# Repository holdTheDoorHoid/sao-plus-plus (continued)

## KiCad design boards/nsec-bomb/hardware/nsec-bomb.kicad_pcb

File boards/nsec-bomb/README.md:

# NorthSec Bomb — SAO++ edition

The circuit is **Sao_Bomb**, one of the add-ons made for the **NorthSec 2025** badge by the **NorthSec badge team**: https://github.com/nsec/nsec-badge/tree/nsec25/hw/2025/sao/Sao_Bomb (commit 0ea779f, 2025-07-14). Licence: **MIT** (their `LICENSE` is kept in [original/LICENSE](original/LICENSE); no file of this board states an exception).

**The outline and the front art are SAO++'s own drawing** (CC-BY-SA-4.0, [art/nsec-bomb-front.svg](art/nsec-bomb-front.svg)), not NorthSec's. NorthSec drew their board over a picture of a cartoon time bomb whose owner nobody here can identify, so their outline and art are not used and not kept in this repository ([original/README.md](original/README.md) lists exactly what was cut).

> **One art question is still open, and it is the owner's call before anything is sold:** the "nsec 2025" logo on the back is NorthSec's event branding. The MIT licence covers the file, not the use of their name and mark on boards someone else sells. Ask NorthSec, or take the logo off.

## What NorthSec's original is

Their repository does not describe it, so this is read from the files:

- A 53 × 38 mm add-on shaped like a bundle of dynamite with a clock, badge power only: a 2×3 SMD header, four LEDs soldered on the front by hand, each with a 330 Ω resistor.
- **Eight small plated holes, not nine and not sockets.** The survey read them as "pin sockets" because the maker used a socket footprint, but their parts list gives them a quantity of 0: nothing was fitted. Four holes are on the 3.3 V supply ("3v3") and four each lead to one LED ("Conn1" … "Conn4").
- **No LED is connected to anything until you add a wire.** A wire from a 3v3 hole to a Conn hole lights that LED. Those are the bomb's wires; cut one and its light goes out. There is no chip and no game logic: whatever game was played with it at the event was played by people.
- On the back, the "nsec 2025" logo and a 5 × 5 mm white square (purpose not recorded).

## What SAO++ makes of it

The same circuit and the same wire trick on a newly drawn board, working from **either** the badge **or** its own coin cell.

**The drawing (front):** three sticks of dynamite stacked flat, 54 × 38 mm, the middle one 3.5 mm shorter at each end. Two white bands of tape hold them together. "TNT" on the top stick, "DANGER" on the bottom one. Strapped across the middle is a timer box: a white frame with four screws and a display reading **00:07** in bare (gold-plated) copper. Each end of the top and bottom sticks is a detonator: a small bare window with a red LED glowing behind it and, beside it, a numbered wire terminal (1–4). The timer carries four "+" terminals. The builder's own wires, from timer to detonators, finish the picture.

| | NorthSec original (2025) | SAO++ rev A |
|---|---|---|
| Outline and art | Traced by the maker from a third-party picture | Drawn from scratch by `hardware/build_board.py` |
| Connector | 2×3 SMD header, centre of the back | 6-pin SAO v1.69bis shrouded, keyed SMD connector, key slot up, mid-height, 10.5 mm right of centre (front view) |
| Power | Badge only | Slide switch in the middle of the bottom edge: **SAO / OFF / BAT**. CR2032 clip on the back; the cell slides in from the top edge |
| Lights | Four hand-soldered 1206 LEDs on the front | Four **red** LEDs on the back, shining through the board at the four detonators |
| Resistors | 330 Ω (about 4 mA per LED) | 1.3 kΩ (about 1 mA per LED, so a cell lasts) |
| Wire points | Eight 0.7 mm plated holes | Eight **1.6 mm square solder pads, no hole** |
| Back | Logo, white square | Same logo and square, same size. Labels: SAO / OFF / BAT, "CR2032 + UP", pin 1, "BOMB SAO++ rA", "circuit: NorthSec 2025 (MIT)" |

**How to arm it:** solder a short piece of wire on the front from any **+** pad on the timer to a numbered pad. Wire 1 lights the upper-left detonator, 2 upper right, 3 lower left, 4 lower right. Leave the wires looped up off the board so they can be cut. A wire can only ever join the supply to a resistor, so no wiring mistake between these pads can short anything or reach the coin cell.

**Why pads instead of holes:** a wire soldered through a hole leaves a stub on the back, where the coin cell has to slide along the board and rest. Pads keep the back flat. Wires soldered on a pad are easier to fit but may be weaker when tugged; that is untested.

**Parts shared with the rest of SAO++:** connector, switch, cell clip, red through-board LED and 1.3 kΩ resistor: all reels other boards already use. **No new part.** The wire pads are bare copper.

**Battery life (calculated, not measured):** four red LEDs at about 1 mA each is about 4 mA, so a CR2032 should last roughly 35–50 hours with all four wires in place.

## How it fits

Drawing the outline ourselves removed the squeeze the traced outline had:

- **Switch:** the bottom edge is straight for 49 mm, so the switch sits in the middle of it with its knob 1.05 mm past the edge.
- **Cell:** the top edge is straight too. The cell slides in 5 mm from it, between the upper-left LED (0.9 mm clear of the cell's path) and the logo.
- **Clip and connector** sit side by side with 1.8 mm between the clip and the connector's shroud; no keep-out boxes overlap, so the board needs no rule exceptions.
- **LEDs** lie along their sticks, 3.6 mm in from each end, each with its resistor 3.1 mm toward the middle of the board.
- **Front copper:** the supply reaches the four + pads by a thin track that runs under the bottom line of the timer's frame and up each side of the display between the pads; each numbered pad has a 3 mm track to a tiny covered via. Under solder mask these show only faintly.

## Things to check on the first prototype

1. **Wire pads.** Solder four wires, tug them, cut them. If pads lift, make the pads larger or go back to plated holes with badge power only.
2. **Light through the board.** Each LED shines through 1.6 mm of board into a 3.2 × 1.6 mm bare window. `SAOPP-LED-10` is still marked "verify: brightness through 1.6 mm board at 1 mA" in the parts list; this board does not settle that until one is built. If dim, R1–R4 can become 330 Ω (SAOPP-R-02, already approved): about 4 mA each, NorthSec's own value, and well under a day per cell.
3. **Display digits.** The 00:07 is bare copper with strokes 0.6 mm wide, each in its own opening in the solder mask. Check they come out crisp, and that the fab does not object to copper that is connected to nothing.
4. **Switch.** Which way the knob sits for position 1 (the labels assume "knob toward SAO = badge power"; if not, swap the SAO and BAT labels).
5. **Cell clip direction.** The clip fits its pads both ways round; its open side must face the **top** edge. Tell the assembler.
6. **Pin 1 position** against a real v1.69bis badge (same corner as every other SAO++ board).
7. **Hanging.** The connector is 10.5 mm right of centre (front view) with the cell on the other side; check how the board hangs and that it does not strain the badge socket.
8. **Mask colour.** Red is the obvious choice (the SVG in `art/` shows it); the renders above use KiCad's default green.

## Files

- `hardware/nsec-bomb.kicad_pro` — KiCad 10 project. ERC: 0 issues. DRC: 0 errors, 0 warnings, 0 unconnected, schematic matches board.
- `hardware/build_board.py` — draws the whole board: the ART section holds every number of the outline and front art, the PLACEMENT section every part position. It reads only `circuit.json` and the footprint libraries, nothing from `original/`. It also writes `art/nsec-bomb-front.svg` and `hardware/outline.json`.
- `art/nsec-bomb-front.svg` — the front as a picture (red mask, white silkscreen, gold copper), written by the build script.
- `hardware/circuit.json` — the circuit as data; `tools/gen_schematic.py nsec-bomb` then `hardware/fix_schematic.py` (marks the eight bare pads "not in BOM") make the schematic.
- `hardware/nsec-bomb.kicad_dru` — one rule, so the copper display digits are not flagged for being art.
- `hardware/parts_local.py`, `hardware/nsec-bomb-local.pretty/` — the wire pad (bare copper, nothing to buy) and an unchanged copy of NorthSec's logo footprint.
- `production/` — everything a board house needs, for one board (`single/`) and a 2×2 panel (`panel/`). Start with [production/README.md](production/README.md).
- `original/` — NorthSec's circuit files (schematic, footprints, parts list, and the board file with the traced outline and art cut out). See [original/README.md](original/README.md).

## Parts cost (parts only; list prices as dated in docs/parts.md, not re-checked for this board)

| Part | Qty | Each @ ~100 boards |
|---|---|---|
| Connector XFCN BH254VS-6P (LCSC C492445) | 1 | $0.10 |
| Switch C&K PCM13SMTR (Digikey) | 1 | ~$0.90 |
| CR2032 clip TE BAT-HLD-001 (LCSC C7501066) | 1 | $0.61 |
| Red through-board LED LTST-C230KRKT (LCSC C125107) | 4 | $0.037 |
| Resistor 0603 1.3 kΩ (LCSC C22767) | 4 | <$0.01 |
| **Total** | | **about $1.80** |

Not included: the CR2032 cell, the bare board (54 × 38 mm) and the jumper wire.

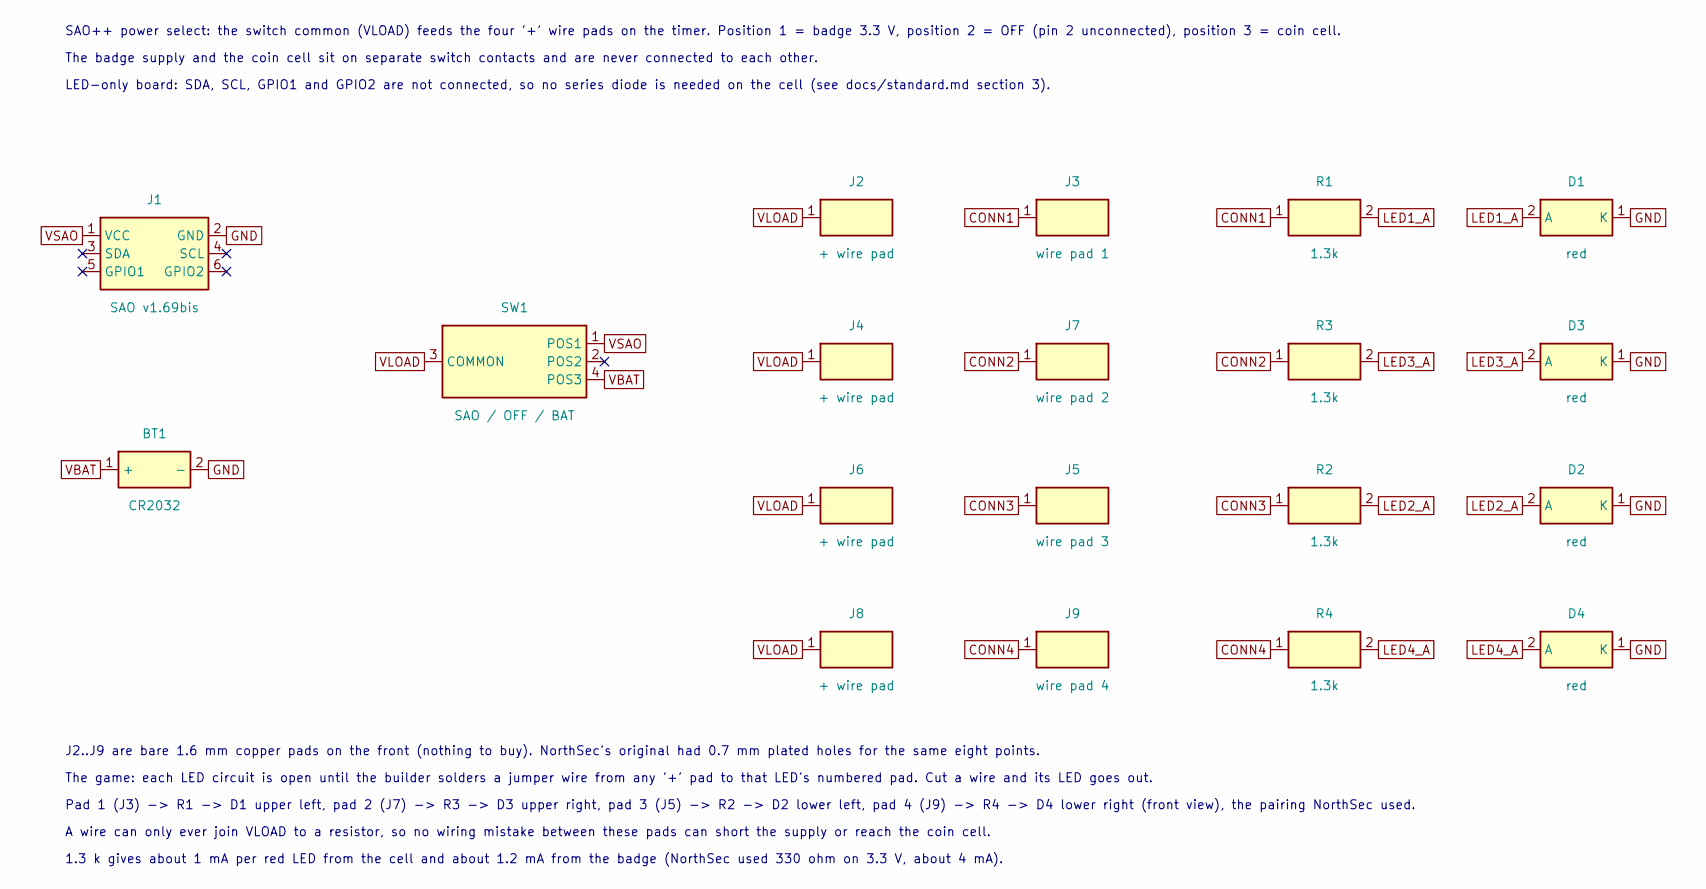
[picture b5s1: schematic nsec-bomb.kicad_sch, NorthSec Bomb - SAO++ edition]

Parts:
BT1: CR2032; SAOPP_BAT-01_CR2032_SMD_TE_BAT-HLD-001; MPN BAT-HLD-001; LCSC C7501066
D1, D2, D3, D4: red; SAOPP_LED-10_1206_ReverseMount_ThroughBoard; MPN LTST-C230KRKT; LCSC C125107
J1: SAO v1.69bis; SAOPP_CONN-01_BoxHeader_2x03_P2.54mm_SMD_XFCN_BH254VS-6P; MPN BH254VS-6P; LCSC C492445
J2, J4, J6, J8: + wire pad; WirePad_1.6x1.6mm; MPN none: bare pad, nothing fitted
J3: wire pad 1; WirePad_1.6x1.6mm; MPN none: bare pad, nothing fitted
J5: wire pad 3; WirePad_1.6x1.6mm; MPN none: bare pad, nothing fitted
J7: wire pad 2; WirePad_1.6x1.6mm; MPN none: bare pad, nothing fitted
J9: wire pad 4; WirePad_1.6x1.6mm; MPN none: bare pad, nothing fitted
R1, R2, R3, R4: 1.3k; SAOPP_R_0603_1608Metric; MPN 0603WAF1301T5E; LCSC C22767
SW1: SAO / OFF / BAT; SAOPP_SW-01_Slide_SP3T_CK_PCM13SMTR; MPN PCM13SMTR; LCSC C221842

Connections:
CONN1: J3.1, R1.1
CONN2: J7.1, R3.1
CONN3: J5.1, R2.1
CONN4: J9.1, R4.1
GND: BT1.2 (-), D1.1 (K), D2.1 (K), D3.1 (K), D4.1 (K), J1.2 (GND)
LED1_A: D1.2 (A), R1.2
LED2_A: D2.2 (A), R2.2
LED3_A: D3.2 (A), R3.2
LED4_A: D4.2 (A), R4.2
VBAT: BT1.1 (+), SW1.4 (POS3)
VLOAD: J2.1, J4.1, J6.1, J8.1, SW1.3 (COMMON)
VSAO: J1.1 (VCC), SW1.1 (POS1)

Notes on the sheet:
SAO++ power select: the switch common (VLOAD) feeds the four '+' wire pads on the timer. Position 1 = badge 3.3 V, position 2 = OFF (pin 2 unconnected), position 3 = coin cell.
The badge supply and the coin cell sit on separate switch contacts and are never connected to each other.
LED-only board: SDA, SCL, GPIO1 and GPIO2 are not connected, so no series diode is needed on the cell (see docs/standard.md section 3).
J2..J9 are bare 1.6 mm copper pads on the front (nothing to buy). NorthSec's original had 0.7 mm plated holes for the same eight points.
The game: each LED circuit is open until the builder solders a jumper wire from any '+' pad to that LED's numbered pad. Cut a wire and its LED goes out.
Pad 1 (J3) -> R1 -> D1 upper left, pad 2 (J7) -> R3 -> D3 upper right, pad 3 (J5) -> R2 -> D2 lower left, pad 4 (J9) -> R4 -> D4 lower right (front view), the pairing NorthSec used.
A wire can only ever join VLOAD to a resistor, so no wiring mistake between these pads can short the supply or reach the coin cell.
1.3 k gives about 1 mA per red LED from the cell and about 1.2 mA from the badge (NorthSec used 330 ohm on 3.3 V, about 4 mA).

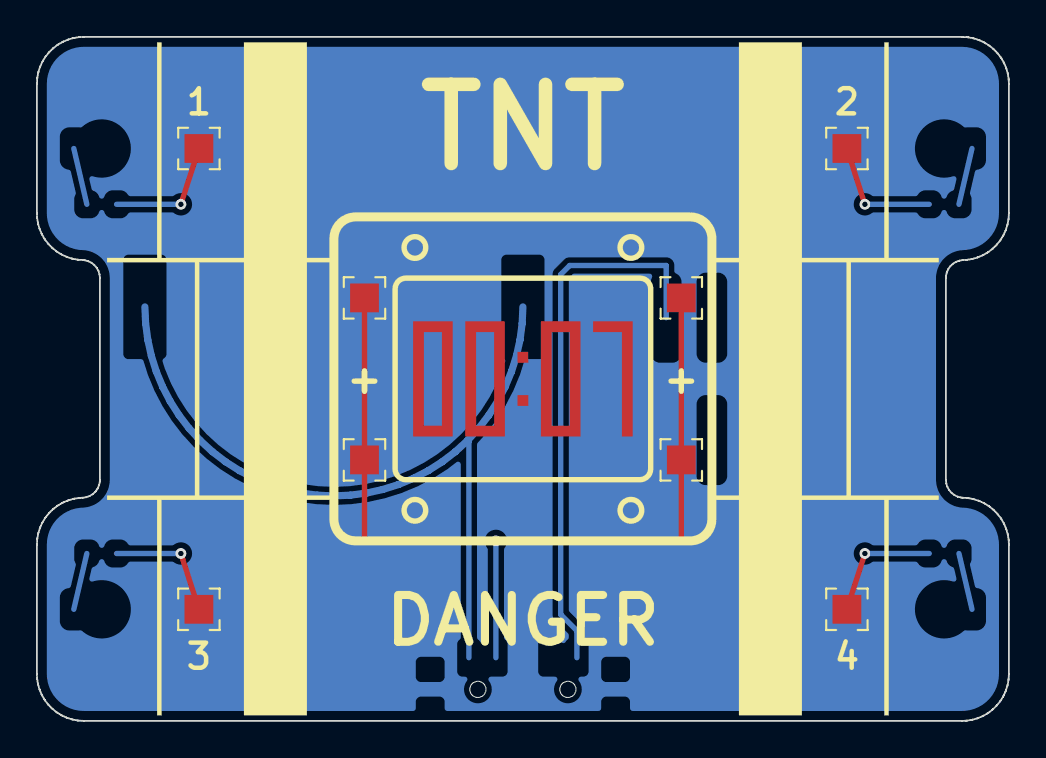
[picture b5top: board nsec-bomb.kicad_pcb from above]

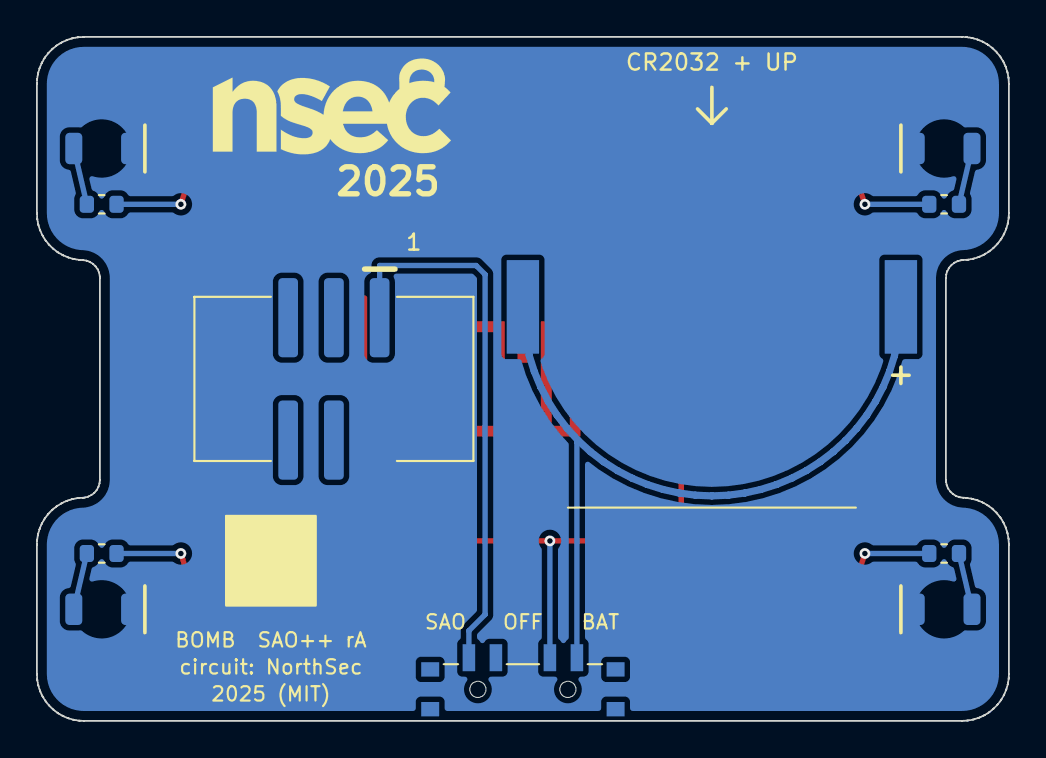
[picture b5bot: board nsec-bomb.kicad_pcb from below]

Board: 2 copper layers, 54.0 x 38.0 mm, 19 parts (11 on the bottom side), 12 nets.

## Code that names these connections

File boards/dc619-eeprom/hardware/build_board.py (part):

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  - J1, the 6-pin SAO v1.69bis header
  - U1, an AT24C02N I2C EEPROM (SOIC-8): A0 A1 A2 to GND (address 0x50), WP to GND (writable), VCC to SAO pin 1,
    SDA / SCL straight to SAO pins 3 / 4. No pull-ups, no supply capacitor
  - R1 4.7k from SAO pin 5 (GPIO1) to LED D2 to GND, and R2 4.7k from SAO pin 6 (GPIO2) to LED D1 to GND: two lights
    the BADGE switches on by driving its GPIO lines high
There is no battery and no switch on it. So everything drawn here (outline, placement, routing, front artwork) is
SAO++'s own; only the circuit is the maker's.
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CONN = (12.0, 9.2)          # centred left-right; pads start 3.6 mm from the top edge, body 4.36 mm from the sides
U1_AT = (11.2, 17.6)        # EEPROM, just below the connector
C1_AT = (7.6, 17.775)       # its supply capacitor, beside it
R1_AT = (2.3, 13.6)         # GPIO1 resistor, in the left margin beside the connector
R2_AT = (17.2, 16.2)        # GPIO2 resistor, below the connector
D2_AT = (4.4, 19.0)         # GPIO1 light, lower left (front view)
D1_AT = (19.6, 19.0)        # GPIO2 light, lower right
VIA_U1 = (11.2, 20.2)       # ground via below the EEPROM
VIA_J1 = (5.6, 9.25)        # ground via under the connector body

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_NS = uuid.UUID("5a0b1b15-0000-4000-8000-00000000a011")          # same namespace as tools/gen_schematic.py

# the maker's circuit, checked against the schematic picture every build
assert PADNETS["J1"] == {"1": "VSAO", "2": "GND", "3": "SDA", "4": "SCL", "5": "SAO_GPIO1", "6": "SAO_GPIO2"}
assert PADNETS["U1"] == {"1": "SCL", "2": "GND", "3": "SDA", "4": "VSAO", "5": "GND"}     # SOT-23-5: 5 = WP, tied low
assert all(len(d) == len(PINNAMES[r]) for r, d in PADNETS.items()), "every pin is wired on this board"

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conn = place("J1", CONN, ("1", (CONN[0] - 2.54, CONN[1] - 3.4)))          # VCC top-left in front view = key slot up
u1 = place("U1", U1_AT, ("1", (U1_AT[0] + 1.1375, U1_AT[1] - 0.95)))       # SCL / GND / SDA column on the right
c1 = place("C1", C1_AT, ("1", (C1_AT[0], C1_AT[1] + 0.775)))               # supply pad at the bottom, level with U1 pin 4
r1 = place("R1", R1_AT, ("1", (R1_AT[0], R1_AT[1] - 0.825)))               # GPIO1 enters at the top
r2 = place("R2", R2_AT, ("1", (R2_AT[0] - 0.825, R2_AT[1])))               # GPIO2 enters on the left
d2 = place("D2", D2_AT, ("2", (D2_AT[0] - 1.55, D2_AT[1])))                # anode toward the left edge
d1 = place("D1", D1_AT, ("2", (D1_AT[0] - 1.55, D1_AT[1])))                # anode toward the middle
LEDS = {"D1": D1_AT, "D2": D2_AT}

# connector pin order, as docs/standard.md section 1 draws it (seen from the front it is mirrored: VCC SDA GPIO1 / GND SCL GPIO2)
def near(a, b, tol=0.002):
    return abs(a[0] - b[0]) < tol and abs(a[1] - b[1]) < tol

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u3 = pp(u1, "3")
SX = ux + 2.7
route("SDA", [pp(conn, "3"), (cx, MID), (LANE_R, MID + 1.27), (LANE_R, BELOW + 0.2), (SX, BELOW + 0.2 + (SX - LANE_R)), (SX, u3[1]), u3])
# GPIO2: pin 6 (bottom right) -> R2 -> the right-hand light
r2a, r2b = pp(r2, "1"), pp(r2, "2")
route("SAO_GPIO2", [pp(conn, "6"), (cx + 2.54, r2a[1] - 0.8), (cx + 2.54 + 0.8, r2a[1]), r2a])
d1a = pp(d1, "2")
route("LED1_A", [r2b, (d1a[0], r2b[1] + 0.7), d1a])
# GPIO1: pin 5 (top right) -> along the top edge above the connector -> down the left margin -> R1 -> the left-hand light
TOPY, LEFTX = cy - 3.4 - 2.2 - 0.8, R1_AT[0]
route("SAO_GPIO1", [pp(conn, "5"), (cx + 2.54, TOPY + 0.4), (cx + 2.54 - 0.4, TOPY), (LEFTX + 0.8, TOPY), (LEFTX, TOPY + 0.8), pp(r1, "1")])
d2a = pp(d2, "2")
route("LED2_A", [pp(r1, "2"), (LEFTX, d2a[1] - 1.1), (d2a[0], d2a[1] - 1.1 + (d2a[0] - LEFTX)), d2a])
# ground: the EEPROM's GND pin (middle right) and WP pin (upper left) are boxed in by its other pins, so they are
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
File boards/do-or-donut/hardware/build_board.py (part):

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# The maker's matrix lines broken by the new parts first, then the new nets, shortest first; supplies last.
ORDER = [*[(n, "sig", SIG_W) for n in MATRIX_NETS], ("GND", "pwr2", PWR2_W),
         ("SDB", "sig", SIG_W), ("R_EXT", "sig", SIG_W), ("C_FILT", "sig", SIG_W), ("LED_SDA", "sig", SIG_W), ("LED_SCL", "sig", SIG_W),
         ("D7_RX", "sig", SIG_W), ("D6_TX", "sig", SIG_W), ("SAO_GPIO1", "sig", SIG_W), ("SAO_GPIO2", "sig", SIG_W),
         ("SDA", "sig", SIG_W), ("SCL", "sig", SIG_W), ("OFF_SENSE", "sig", SIG_W),
         ("BAT+", "pwr", PWR_W), ("VSAO", "pwr2", PWR2_W), ("V3V3", "pwr2", PWR2_W)]
# Ground goes last and rips nothing: what it cannot reach by track, the back ground pour joins (checked by DRC).
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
